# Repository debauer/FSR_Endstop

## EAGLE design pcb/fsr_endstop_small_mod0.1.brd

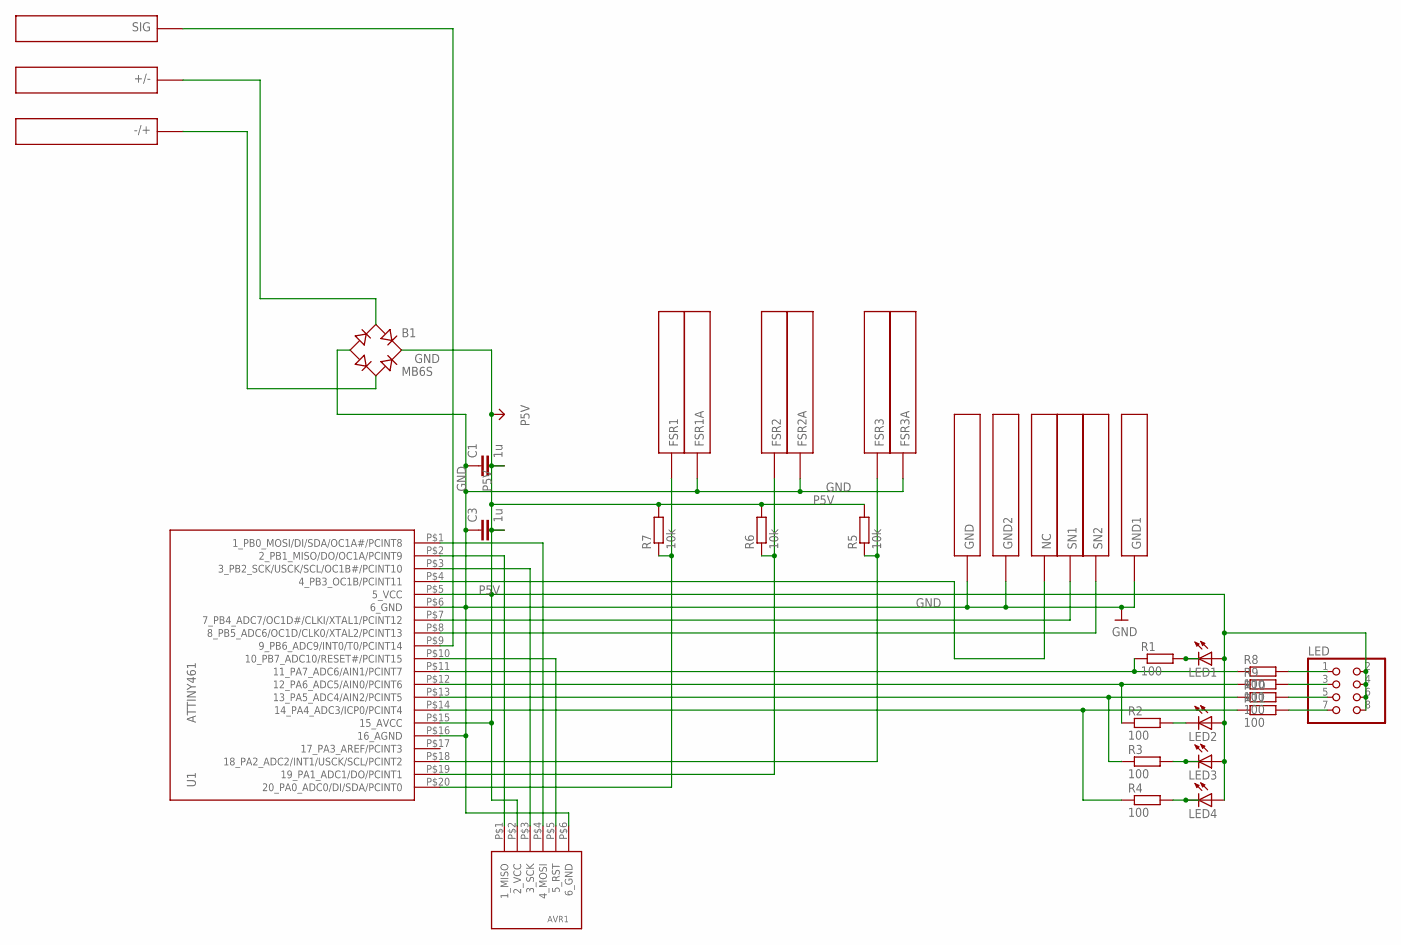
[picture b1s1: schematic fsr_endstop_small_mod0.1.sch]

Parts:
+/-: PIN1.2MM; PIN_1.2MM
-/+: PIN1.2MM; PIN_1.2MM
AVR1: AVR6
B1: MB6S; SOIC-4
C1, C3: 1u; C0805
FSR1, FSR1A, FSR2, FSR2A, FSR3, FSR3A: PIN1.2MM; PIN_1.2MM
GND, GND1, GND2: PIN1.2MM; PIN_1.2MM
LED: PINHD-2X4; 2X04
LED1, LED2, LED3, LED4: LEDCHIP-LED0805; CHIP-LED0805
NC: PIN1.2MM; PIN_1.2MM
R1, R2, R3, R4, R8, R9, R10, R11: 100; R0805
R5, R6, R7: 10k; R0805
SIG: PIN1.2MM; PIN_1.2MM
SN1, SN2: PIN1.2MM; PIN_1.2MM
U1: ATTINY461; SOIC-20

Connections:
GND: AVR1.P$6 (6_GND), B1.-, C1.1, C3.1, FSR1A.P$1, FSR2A.P$1, FSR3A.P$1, GND.P$1, GND1.P$1, GND2.P$1, U1.P$6 (6_GND), U1.P$16 (16_AGND)
unnamed: AVR1.P$4 (4_MOSI), U1.P$1 (1_PB0_MOSI/DI/SDA/OC1A#/PCINT8)
unnamed: AVR1.P$1 (1_MISO), U1.P$2 (2_PB1_MISO/DO/OC1A/PCINT9)
unnamed: -/+.P$1, B1.~2 (AC2)
unnamed: +/-.P$1, B1.~1 (AC1)
unnamed: AVR1.P$3 (3_SCK), U1.P$3 (3_PB2_SCK/USCK/SCL/OC1B#/PCINT10)
unnamed: AVR1.P$5 (5_RST), U1.P$10 (10_PB7_ADC10/RESET#/PCINT15)
unnamed: FSR1.P$1, R7.1, U1.P$20 (20_PA0_ADC0/DI/SDA/PCINT0)
unnamed: FSR2.P$1, R6.1, U1.P$19 (19_PA1_ADC1/DO/PCINT1)
unnamed: FSR3.P$1, R5.1, U1.P$18 (18_PA2_ADC2/INT1/USCK/SCL/PCINT2)
unnamed: R4.1, R11.1, U1.P$14 (14_PA4_ADC3/ICP0/PCINT4)
unnamed: R3.1, R10.1, U1.P$13 (13_PA5_ADC4/AIN2/PCINT5)
unnamed: R2.1, R9.1, U1.P$12 (12_PA6_ADC5/AIN0/PCINT6)
unnamed: R1.1, R8.1, U1.P$11 (11_PA7_ADC6/AIN1/PCINT7)
unnamed: SIG.P$1, U1.P$9 (9_PB6_ADC9/INT0/T0/PCINT14)
unnamed: NC.P$1, U1.P$4 (4_PB3_OC1B/PCINT11)
unnamed: SN2.P$1, U1.P$8 (8_PB5_ADC6/OC1D/CLK0/XTAL2/PCINT13)
unnamed: SN1.P$1, U1.P$7 (7_PB4_ADC7/OC1D#/CLKI/XTAL1/PCINT12)
unnamed: LED1.C, R1.2
unnamed: LED2.C, R2.2
unnamed: LED3.C, R3.2
unnamed: LED4.C, R4.2
unnamed: LED.7, R11.2
unnamed: LED.1, R8.2
unnamed: LED.3, R9.2
unnamed: LED.5, R10.2
P5V: AVR1.P$2 (2_VCC), B1.+, C1.2, C3.2, LED.2, LED.4, LED.6, LED.8, LED1.A, LED2.A, LED3.A, LED4.A, R5.2, R6.2, R7.2, U1.P$5 (5_VCC), U1.P$15 (15_AVCC)

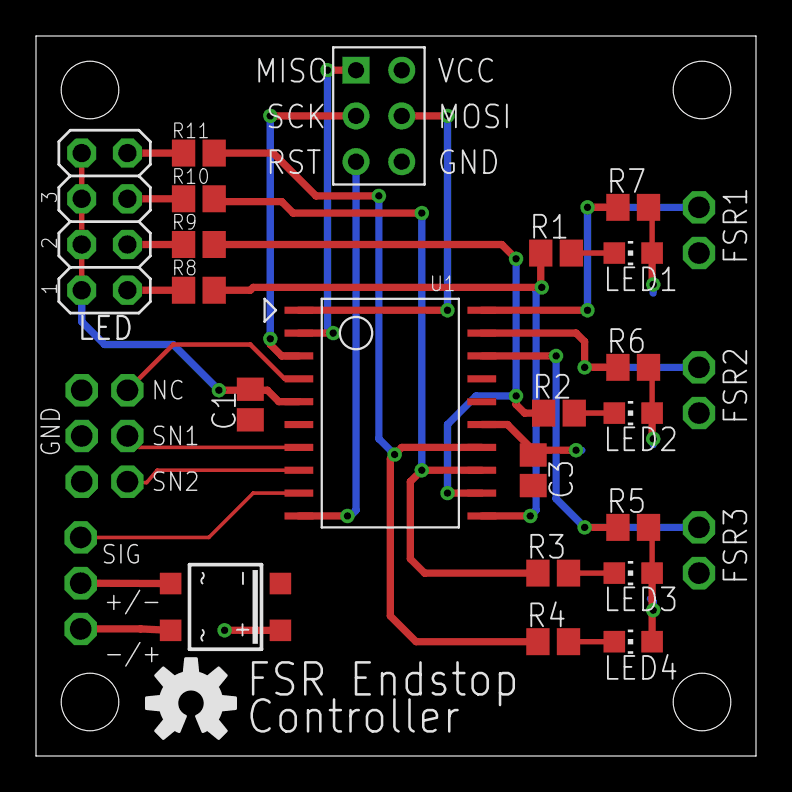
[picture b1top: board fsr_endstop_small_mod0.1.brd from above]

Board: 2 copper layers, 40.0 x 40.0 mm, 38 parts (1 on the bottom side), 27 nets.

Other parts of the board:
U$1, U$2: OSHW-LOGO-M

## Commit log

2016-04-13 mod eagle files added

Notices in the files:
parts and their libraries:
SparkFun-Aesthetics: Licensing: Creative Commons ShareAlike 4.0 International - https://creativecommons.org/licenses/by-sa/4.0
